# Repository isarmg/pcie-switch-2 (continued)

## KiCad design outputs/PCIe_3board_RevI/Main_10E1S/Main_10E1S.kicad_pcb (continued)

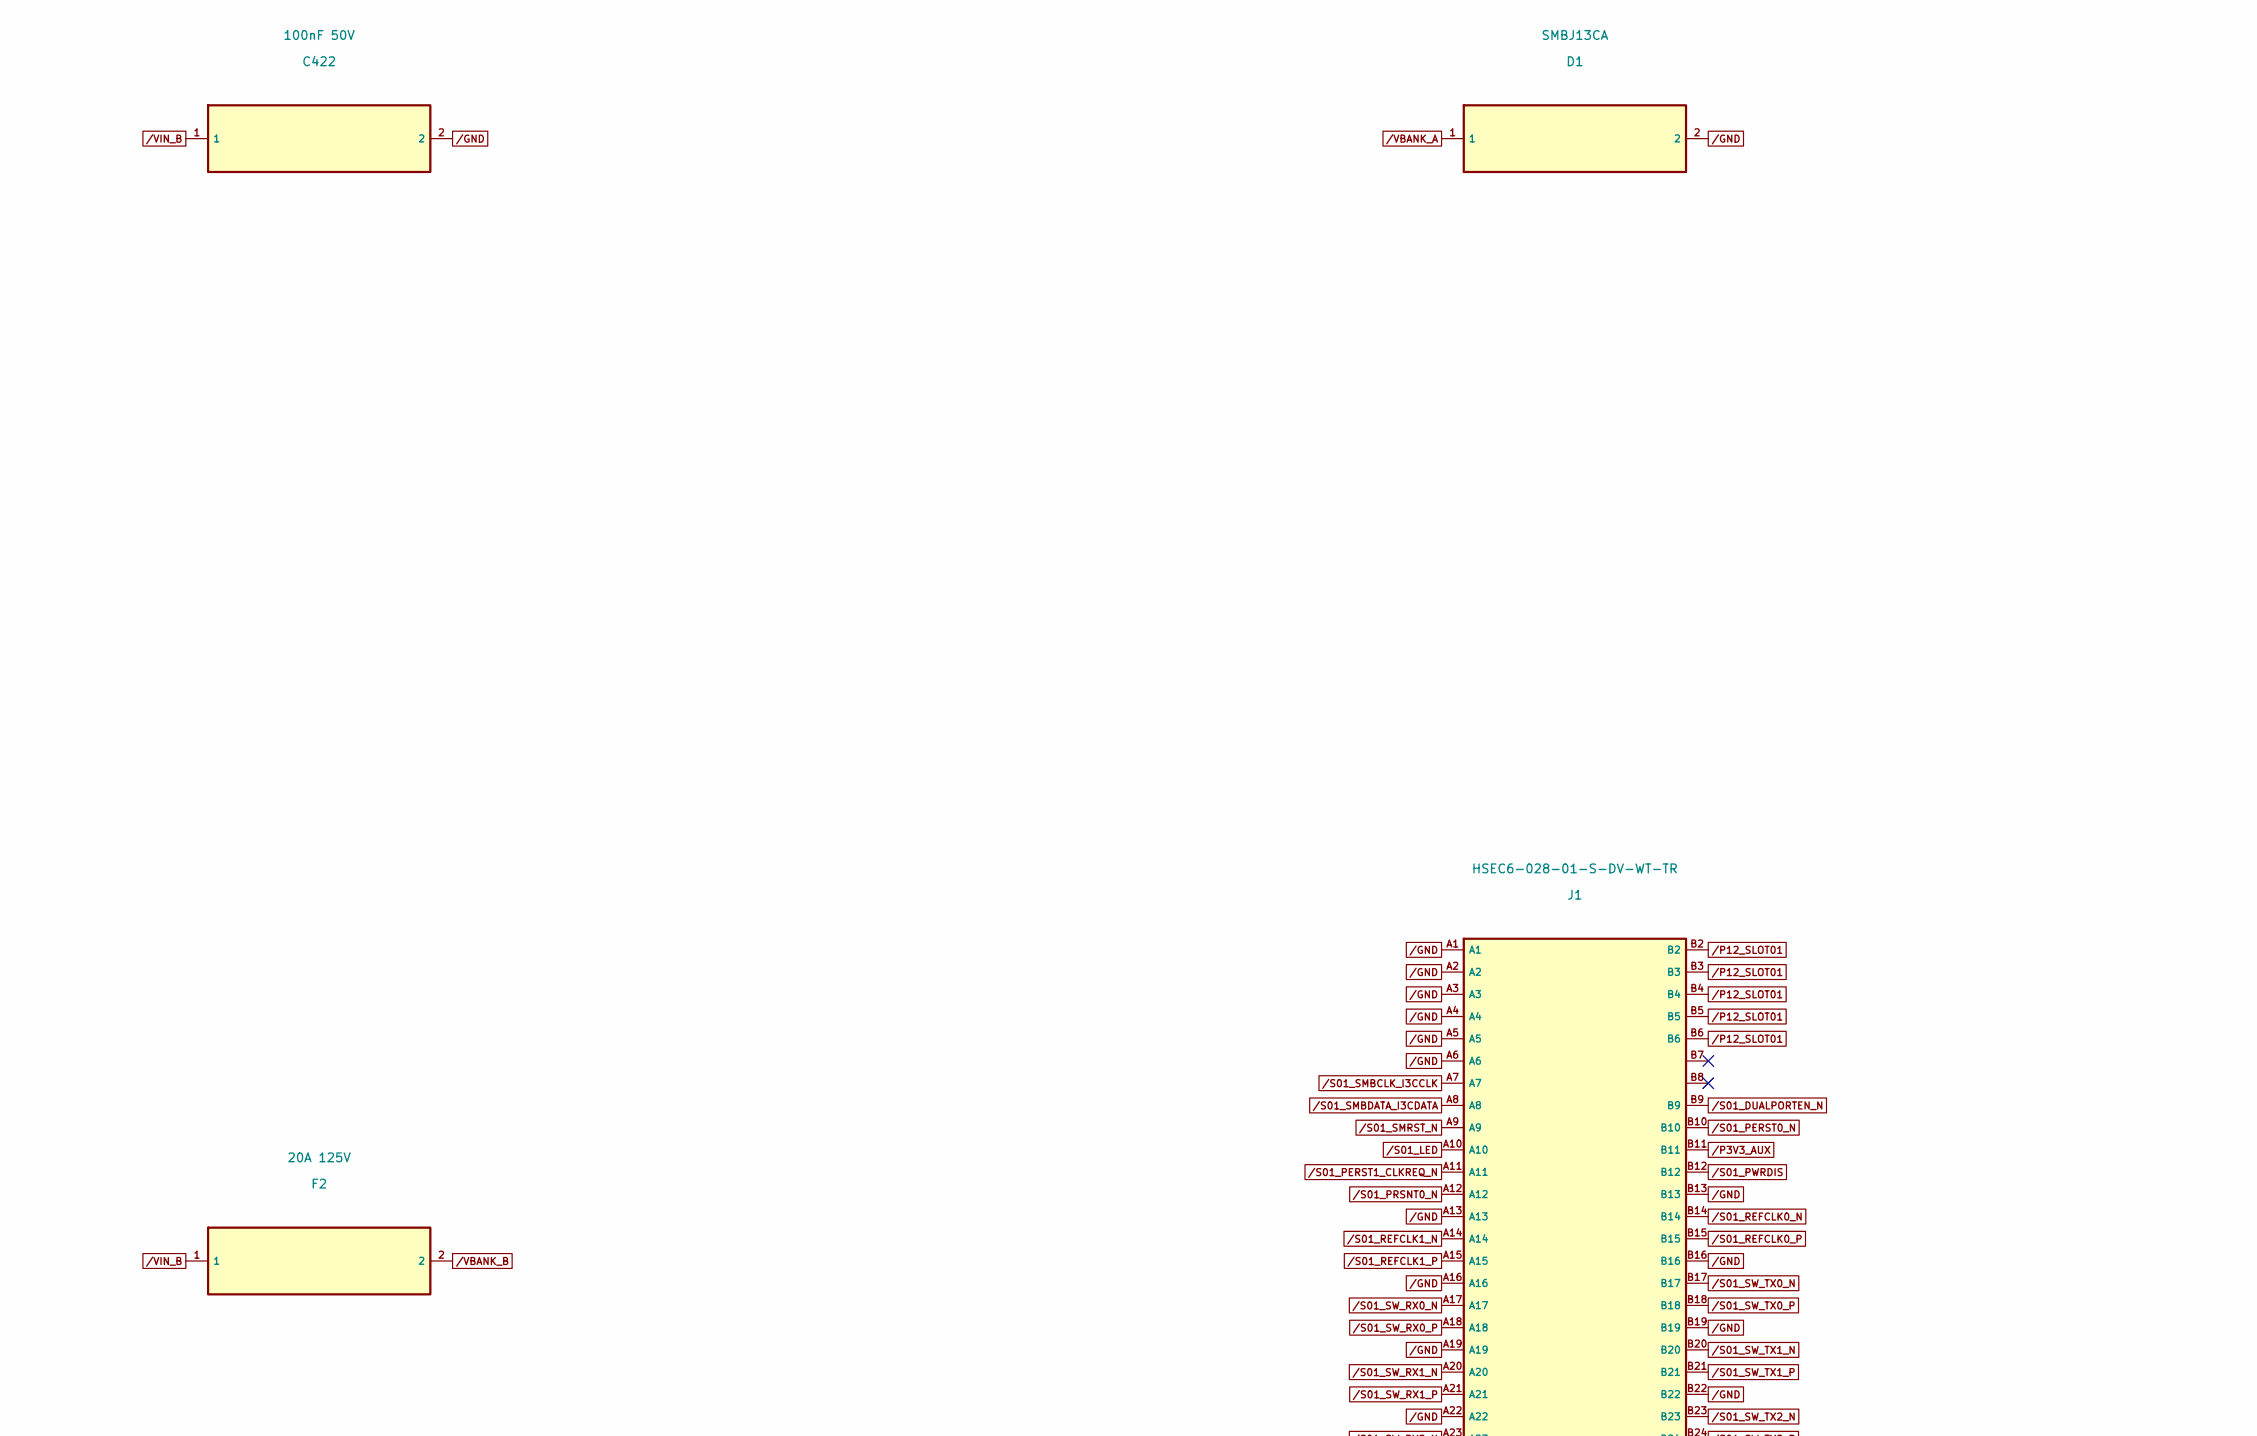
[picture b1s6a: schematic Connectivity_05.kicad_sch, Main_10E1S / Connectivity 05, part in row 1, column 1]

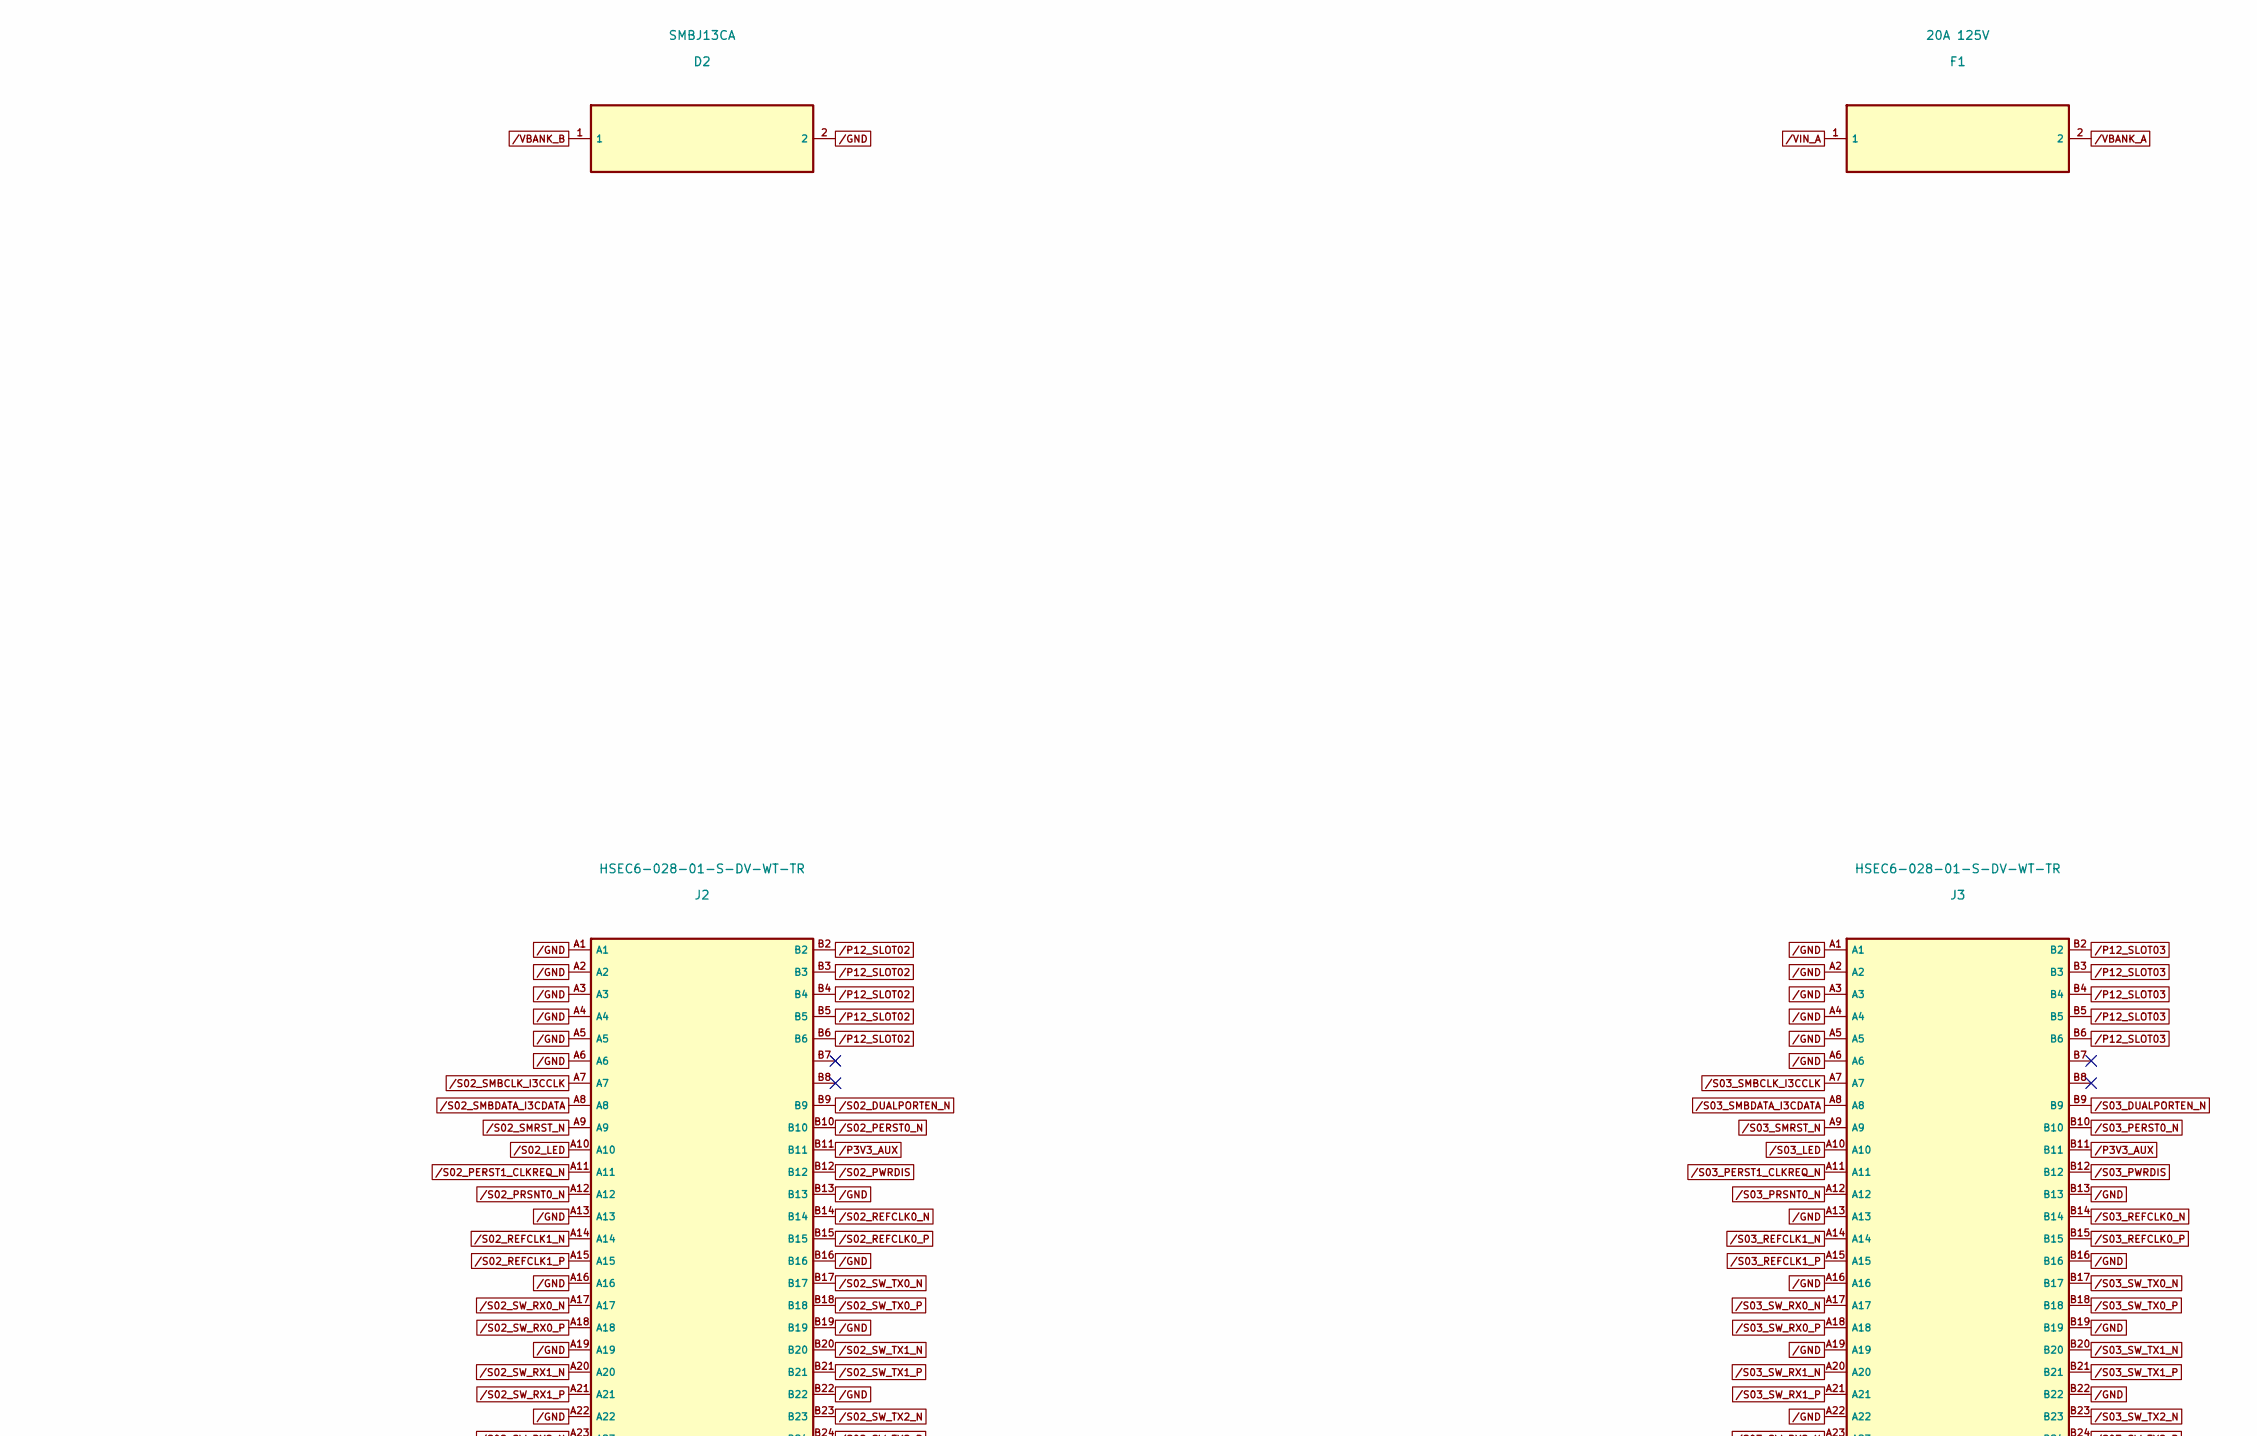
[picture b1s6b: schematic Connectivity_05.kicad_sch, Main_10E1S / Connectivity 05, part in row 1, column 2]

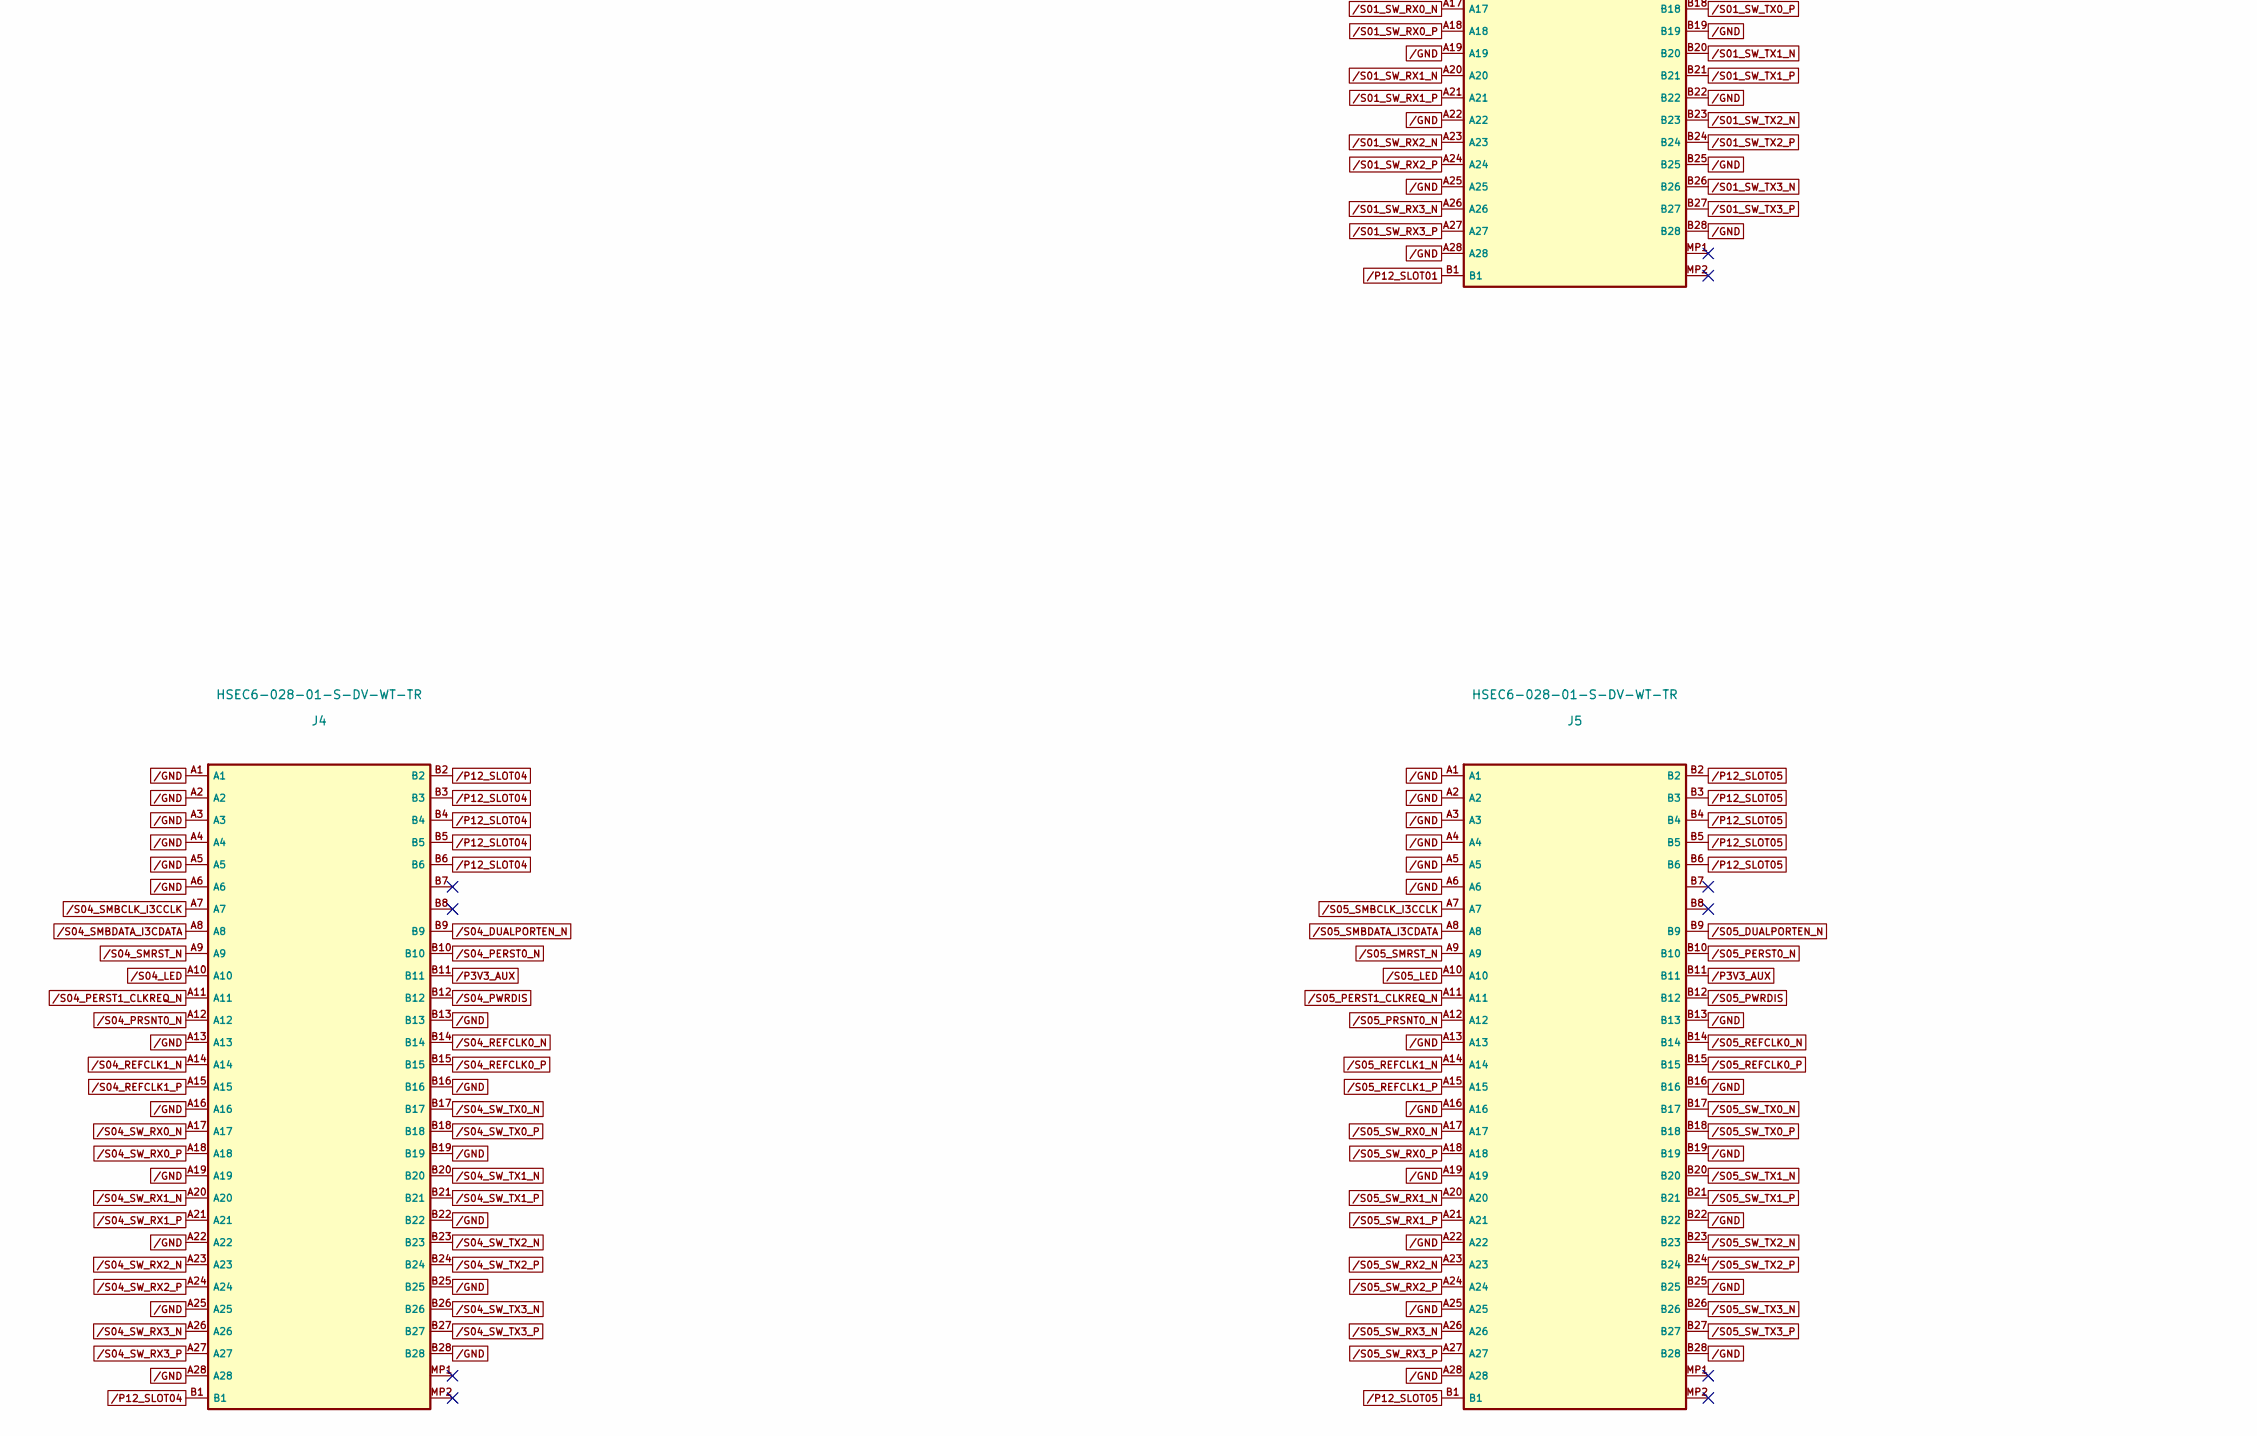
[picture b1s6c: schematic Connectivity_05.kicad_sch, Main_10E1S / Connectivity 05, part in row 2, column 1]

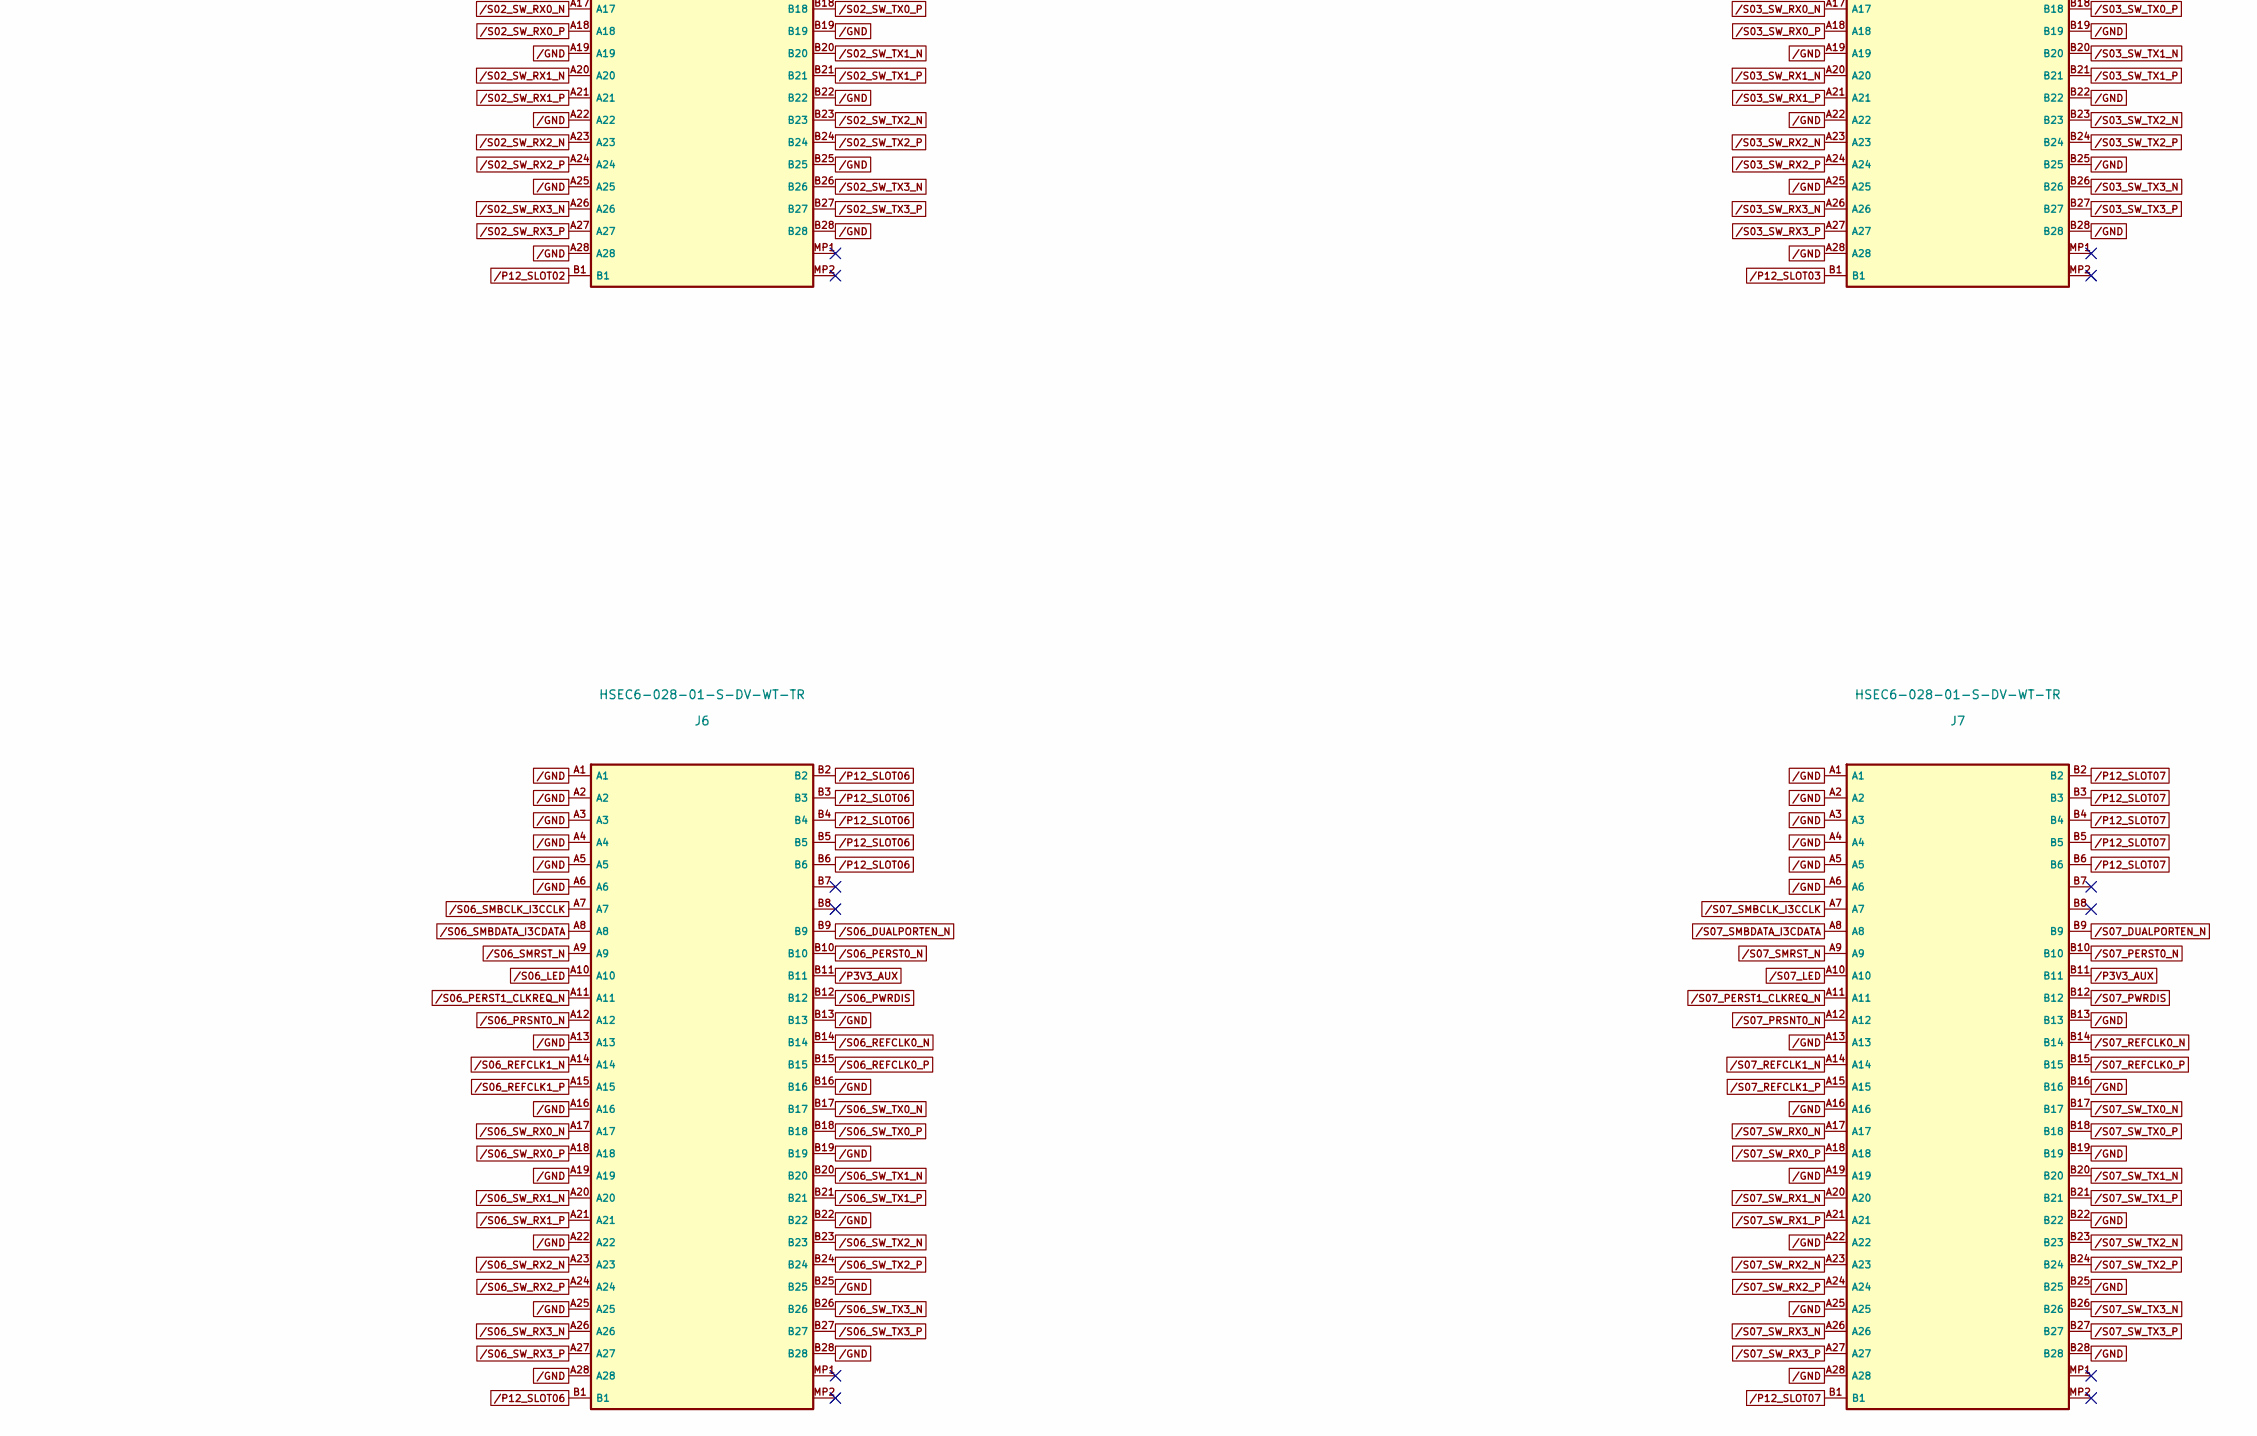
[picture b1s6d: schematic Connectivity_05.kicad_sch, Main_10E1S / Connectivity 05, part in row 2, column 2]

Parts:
C422: 100nF 50V; C_0603_1608Metric
D1, D2: SMBJ13CA; D_SMB
F1, F2: 20A 125V; Littelfuse_456_20A
J1, J2, J3, J4, J5, J6, J7: HSEC6-028-01-S-DV-WT-TR; Samtec_HSEC6-028-01-S-DV-WT

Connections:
/GND: C422.2, D1.2, D2.2, J1.A1, J1.A2, J1.A3, J1.A4, J1.A5, J1.A6, J1.A13, J1.A16, J1.A19, J1.A22, J1.A25, J1.A28, J1.B13, J1.B16, J1.B19, J1.B22, J1.B25, J1.B28, J2.A1, J2.A2, J2.A3, J2.A4, J2.A5, J2.A6, J2.A13, J2.A16, J2.A19, J2.A22, J2.A25, J2.A28, J2.B13, J2.B16, J2.B19, J2.B22, J2.B25, J2.B28, J3.A1, J3.A2, J3.A3, J3.A4, J3.A5, J3.A6, J3.A13, J3.A16, J3.A19, J3.A22, J3.A25, J3.A28, J3.B13, J3.B16, J3.B19, J3.B22, J3.B25, J3.B28, J4.A1, J4.A2, J4.A3, J4.A4, J4.A5, J4.A6, J4.A13, J4.A16, J4.A19, J4.A22, J4.A25, J4.A28, J4.B13, J4.B16, J4.B19, J4.B22, J4.B25, J4.B28, J5.A1, J5.A2, J5.A3, J5.A4, J5.A5, J5.A6, J5.A13, J5.A16, J5.A19, J5.A22, J5.A25, J5.A28, J5.B13, J5.B16, J5.B19, J5.B22, J5.B25, J5.B28, J6.A1, J6.A2, J6.A3, J6.A4, J6.A5, J6.A6, J6.A13, J6.A16, J6.A19, J6.A22, J6.A25, J6.A28, J6.B13, J6.B16, J6.B19, J6.B22, J6.B25, J6.B28, J7.A1, J7.A2, J7.A3, J7.A4, J7.A5, J7.A6, J7.A13, J7.A16, J7.A19, J7.A22, J7.A25, J7.A28, J7.B13, J7.B16, J7.B19, J7.B22, J7.B25, J7.B28; also elsewhere on the board
/P3V3_AUX: J1.B11, J2.B11, J3.B11, J4.B11, J5.B11, J6.B11, J7.B11; also elsewhere on the board
/P12_SLOT01: J1.B1, J1.B2, J1.B3, J1.B4, J1.B5, J1.B6; also elsewhere on the board
/P12_SLOT02: J2.B1, J2.B2, J2.B3, J2.B4, J2.B5, J2.B6; also elsewhere on the board
/P12_SLOT03: J3.B1, J3.B2, J3.B3, J3.B4, J3.B5, J3.B6; also elsewhere on the board
/P12_SLOT04: J4.B1, J4.B2, J4.B3, J4.B4, J4.B5, J4.B6; also elsewhere on the board
/P12_SLOT05: J5.B1, J5.B2, J5.B3, J5.B4, J5.B5, J5.B6; also elsewhere on the board
/P12_SLOT06: J6.B1, J6.B2, J6.B3, J6.B4, J6.B5, J6.B6; also elsewhere on the board
/P12_SLOT07: J7.B1, J7.B2, J7.B3, J7.B4, J7.B5, J7.B6; also elsewhere on the board
/S01_DUALPORTEN_N: J1.B9
/S01_LED: J1.A10
/S01_PERST0_N: J1.B10; also elsewhere on the board
/S01_PERST1_CLKREQ_N: J1.A11
/S01_PRSNT0_N: J1.A12
/S01_PWRDIS: J1.B12
/S01_REFCLK0_N: J1.B14; also elsewhere on the board
/S01_REFCLK0_P: J1.B15; also elsewhere on the board
/S01_REFCLK1_N: J1.A14; also elsewhere on the board
/S01_REFCLK1_P: J1.A15; also elsewhere on the board
/S01_SMBCLK_I3CCLK: J1.A7
/S01_SMBDATA_I3CDATA: J1.A8
/S01_SMRST_N: J1.A9
/S01_SW_RX0_N: J1.A17; also elsewhere on the board
/S01_SW_RX0_P: J1.A18; also elsewhere on the board
/S01_SW_RX1_N: J1.A20; also elsewhere on the board
/S01_SW_RX1_P: J1.A21; also elsewhere on the board
/S01_SW_RX2_N: J1.A23; also elsewhere on the board
/S01_SW_RX2_P: J1.A24; also elsewhere on the board
/S01_SW_RX3_N: J1.A26; also elsewhere on the board
/S01_SW_RX3_P: J1.A27; also elsewhere on the board
/S01_SW_TX0_N: J1.B17; also elsewhere on the board
/S01_SW_TX0_P: J1.B18; also elsewhere on the board
/S01_SW_TX1_N: J1.B20; also elsewhere on the board
/S01_SW_TX1_P: J1.B21; also elsewhere on the board
/S01_SW_TX2_N: J1.B23; also elsewhere on the board
/S01_SW_TX2_P: J1.B24; also elsewhere on the board
/S01_SW_TX3_N: J1.B26; also elsewhere on the board
/S01_SW_TX3_P: J1.B27; also elsewhere on the board
/S02_DUALPORTEN_N: J2.B9
/S02_LED: J2.A10
/S02_PERST0_N: J2.B10; also elsewhere on the board
/S02_PERST1_CLKREQ_N: J2.A11
/S02_PRSNT0_N: J2.A12
/S02_PWRDIS: J2.B12
/S02_REFCLK0_N: J2.B14; also elsewhere on the board
/S02_REFCLK0_P: J2.B15; also elsewhere on the board
/S02_REFCLK1_N: J2.A14; also elsewhere on the board
/S02_REFCLK1_P: J2.A15; also elsewhere on the board
/S02_SMBCLK_I3CCLK: J2.A7
/S02_SMBDATA_I3CDATA: J2.A8
/S02_SMRST_N: J2.A9
/S02_SW_RX0_N: J2.A17; also elsewhere on the board
/S02_SW_RX0_P: J2.A18; also elsewhere on the board
/S02_SW_RX1_N: J2.A20; also elsewhere on the board
/S02_SW_RX1_P: J2.A21; also elsewhere on the board
/S02_SW_RX2_N: J2.A23; also elsewhere on the board
/S02_SW_RX2_P: J2.A24; also elsewhere on the board
/S02_SW_RX3_N: J2.A26; also elsewhere on the board
/S02_SW_RX3_P: J2.A27; also elsewhere on the board
/S02_SW_TX0_N: J2.B17; also elsewhere on the board
/S02_SW_TX0_P: J2.B18; also elsewhere on the board
/S02_SW_TX1_N: J2.B20; also elsewhere on the board
/S02_SW_TX1_P: J2.B21; also elsewhere on the board
/S02_SW_TX2_N: J2.B23; also elsewhere on the board
/S02_SW_TX2_P: J2.B24; also elsewhere on the board
/S02_SW_TX3_N: J2.B26; also elsewhere on the board
/S02_SW_TX3_P: J2.B27; also elsewhere on the board
/S03_DUALPORTEN_N: J3.B9
/S03_LED: J3.A10
/S03_PERST0_N: J3.B10; also elsewhere on the board
/S03_PERST1_CLKREQ_N: J3.A11
/S03_PRSNT0_N: J3.A12
/S03_PWRDIS: J3.B12
/S03_REFCLK0_N: J3.B14; also elsewhere on the board
/S03_REFCLK0_P: J3.B15; also elsewhere on the board
/S03_REFCLK1_N: J3.A14; also elsewhere on the board
/S03_REFCLK1_P: J3.A15; also elsewhere on the board
/S03_SMBCLK_I3CCLK: J3.A7
/S03_SMBDATA_I3CDATA: J3.A8
/S03_SMRST_N: J3.A9
/S03_SW_RX0_N: J3.A17; also elsewhere on the board
/S03_SW_RX0_P: J3.A18; also elsewhere on the board
/S03_SW_RX1_N: J3.A20; also elsewhere on the board
/S03_SW_RX1_P: J3.A21; also elsewhere on the board
/S03_SW_RX2_N: J3.A23; also elsewhere on the board
/S03_SW_RX2_P: J3.A24; also elsewhere on the board
/S03_SW_RX3_N: J3.A26; also elsewhere on the board
/S03_SW_RX3_P: J3.A27; also elsewhere on the board
/S03_SW_TX0_N: J3.B17; also elsewhere on the board
/S03_SW_TX0_P: J3.B18; also elsewhere on the board
/S03_SW_TX1_N: J3.B20; also elsewhere on the board
/S03_SW_TX1_P: J3.B21; also elsewhere on the board
/S03_SW_TX2_N: J3.B23; also elsewhere on the board
/S03_SW_TX2_P: J3.B24; also elsewhere on the board
/S03_SW_TX3_N: J3.B26; also elsewhere on the board
/S03_SW_TX3_P: J3.B27; also elsewhere on the board
/S04_DUALPORTEN_N: J4.B9
/S04_LED: J4.A10
/S04_PERST0_N: J4.B10; also elsewhere on the board
/S04_PERST1_CLKREQ_N: J4.A11
/S04_PRSNT0_N: J4.A12
/S04_PWRDIS: J4.B12
/S04_REFCLK0_N: J4.B14; also elsewhere on the board
/S04_REFCLK0_P: J4.B15; also elsewhere on the board
/S04_REFCLK1_N: J4.A14; also elsewhere on the board
/S04_REFCLK1_P: J4.A15; also elsewhere on the board
/S04_SMBCLK_I3CCLK: J4.A7
/S04_SMBDATA_I3CDATA: J4.A8
/S04_SMRST_N: J4.A9
/S04_SW_RX0_N: J4.A17; also elsewhere on the board
/S04_SW_RX0_P: J4.A18; also elsewhere on the board
/S04_SW_RX1_N: J4.A20; also elsewhere on the board
/S04_SW_RX1_P: J4.A21; also elsewhere on the board
/S04_SW_RX2_N: J4.A23; also elsewhere on the board
/S04_SW_RX2_P: J4.A24; also elsewhere on the board
/S04_SW_RX3_N: J4.A26; also elsewhere on the board
/S04_SW_RX3_P: J4.A27; also elsewhere on the board
/S04_SW_TX0_N: J4.B17; also elsewhere on the board
/S04_SW_TX0_P: J4.B18; also elsewhere on the board
/S04_SW_TX1_N: J4.B20; also elsewhere on the board
/S04_SW_TX1_P: J4.B21; also elsewhere on the board
/S04_SW_TX2_N: J4.B23; also elsewhere on the board
/S04_SW_TX2_P: J4.B24; also elsewhere on the board
/S04_SW_TX3_N: J4.B26; also elsewhere on the board
/S04_SW_TX3_P: J4.B27; also elsewhere on the board
/S05_DUALPORTEN_N: J5.B9
/S05_LED: J5.A10
/S05_PERST0_N: J5.B10; also elsewhere on the board
/S05_PERST1_CLKREQ_N: J5.A11
/S05_PRSNT0_N: J5.A12
/S05_PWRDIS: J5.B12
/S05_REFCLK0_N: J5.B14; also elsewhere on the board
/S05_REFCLK0_P: J5.B15; also elsewhere on the board
/S05_REFCLK1_N: J5.A14; also elsewhere on the board
/S05_REFCLK1_P: J5.A15; also elsewhere on the board
/S05_SMBCLK_I3CCLK: J5.A7
/S05_SMBDATA_I3CDATA: J5.A8
/S05_SMRST_N: J5.A9
/S05_SW_RX0_N: J5.A17; also elsewhere on the board
/S05_SW_RX0_P: J5.A18; also elsewhere on the board
/S05_SW_RX1_N: J5.A20; also elsewhere on the board
/S05_SW_RX1_P: J5.A21; also elsewhere on the board
/S05_SW_RX2_N: J5.A23; also elsewhere on the board
/S05_SW_RX2_P: J5.A24; also elsewhere on the board
/S05_SW_RX3_N: J5.A26; also elsewhere on the board
/S05_SW_RX3_P: J5.A27; also elsewhere on the board
/S05_SW_TX0_N: J5.B17; also elsewhere on the board
/S05_SW_TX0_P: J5.B18; also elsewhere on the board
/S05_SW_TX1_N: J5.B20; also elsewhere on the board
/S05_SW_TX1_P: J5.B21; also elsewhere on the board
/S05_SW_TX2_N: J5.B23; also elsewhere on the board
/S05_SW_TX2_P: J5.B24; also elsewhere on the board
/S05_SW_TX3_N: J5.B26; also elsewhere on the board
/S05_SW_TX3_P: J5.B27; also elsewhere on the board
/S06_DUALPORTEN_N: J6.B9
/S06_LED: J6.A10
/S06_PERST0_N: J6.B10; also elsewhere on the board
/S06_PERST1_CLKREQ_N: J6.A11
/S06_PRSNT0_N: J6.A12
/S06_PWRDIS: J6.B12
/S06_REFCLK0_N: J6.B14; also elsewhere on the board
/S06_REFCLK0_P: J6.B15; also elsewhere on the board
/S06_REFCLK1_N: J6.A14; also elsewhere on the board
/S06_REFCLK1_P: J6.A15; also elsewhere on the board
/S06_SMBCLK_I3CCLK: J6.A7
/S06_SMBDATA_I3CDATA: J6.A8
/S06_SMRST_N: J6.A9
/S06_SW_RX0_N: J6.A17; also elsewhere on the board
/S06_SW_RX0_P: J6.A18; also elsewhere on the board
/S06_SW_RX1_N: J6.A20; also elsewhere on the board
/S06_SW_RX1_P: J6.A21; also elsewhere on the board
/S06_SW_RX2_N: J6.A23; also elsewhere on the board
/S06_SW_RX2_P: J6.A24; also elsewhere on the board
/S06_SW_RX3_N: J6.A26; also elsewhere on the board
/S06_SW_RX3_P: J6.A27; also elsewhere on the board
/S06_SW_TX0_N: J6.B17; also elsewhere on the board
/S06_SW_TX0_P: J6.B18; also elsewhere on the board
/S06_SW_TX1_N: J6.B20; also elsewhere on the board
/S06_SW_TX1_P: J6.B21; also elsewhere on the board
/S06_SW_TX2_N: J6.B23; also elsewhere on the board
/S06_SW_TX2_P: J6.B24; also elsewhere on the board
/S06_SW_TX3_N: J6.B26; also elsewhere on the board
/S06_SW_TX3_P: J6.B27; also elsewhere on the board
/S07_DUALPORTEN_N: J7.B9
/S07_LED: J7.A10
/S07_PERST0_N: J7.B10; also elsewhere on the board
/S07_PERST1_CLKREQ_N: J7.A11
/S07_PRSNT0_N: J7.A12
/S07_PWRDIS: J7.B12
/S07_REFCLK0_N: J7.B14; also elsewhere on the board
/S07_REFCLK0_P: J7.B15; also elsewhere on the board
/S07_REFCLK1_N: J7.A14; also elsewhere on the board
/S07_REFCLK1_P: J7.A15; also elsewhere on the board
/S07_SMBCLK_I3CCLK: J7.A7
/S07_SMBDATA_I3CDATA: J7.A8
/S07_SMRST_N: J7.A9
/S07_SW_RX0_N: J7.A17; also elsewhere on the board
/S07_SW_RX0_P: J7.A18; also elsewhere on the board
/S07_SW_RX1_N: J7.A20; also elsewhere on the board
/S07_SW_RX1_P: J7.A21; also elsewhere on the board
/S07_SW_RX2_N: J7.A23; also elsewhere on the board
/S07_SW_RX2_P: J7.A24; also elsewhere on the board
/S07_SW_RX3_N: J7.A26; also elsewhere on the board
/S07_SW_RX3_P: J7.A27; also elsewhere on the board
/S07_SW_TX0_N: J7.B17; also elsewhere on the board
/S07_SW_TX0_P: J7.B18; also elsewhere on the board
/S07_SW_TX1_N: J7.B20; also elsewhere on the board
/S07_SW_TX1_P: J7.B21; also elsewhere on the board
/S07_SW_TX2_N: J7.B23; also elsewhere on the board
/S07_SW_TX2_P: J7.B24; also elsewhere on the board
/S07_SW_TX3_N: J7.B26; also elsewhere on the board
/S07_SW_TX3_P: J7.B27; also elsewhere on the board
/VBANK_A: D1.1, F1.2; also elsewhere on the board
/VBANK_B: D2.1, F2.2; also elsewhere on the board
/VIN_A: F1.1; also elsewhere on the board
/VIN_B: C422.1, F2.1; also elsewhere on the board
